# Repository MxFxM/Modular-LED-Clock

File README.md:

# Modular-LED-Clock
 Modular design for LED clocks.

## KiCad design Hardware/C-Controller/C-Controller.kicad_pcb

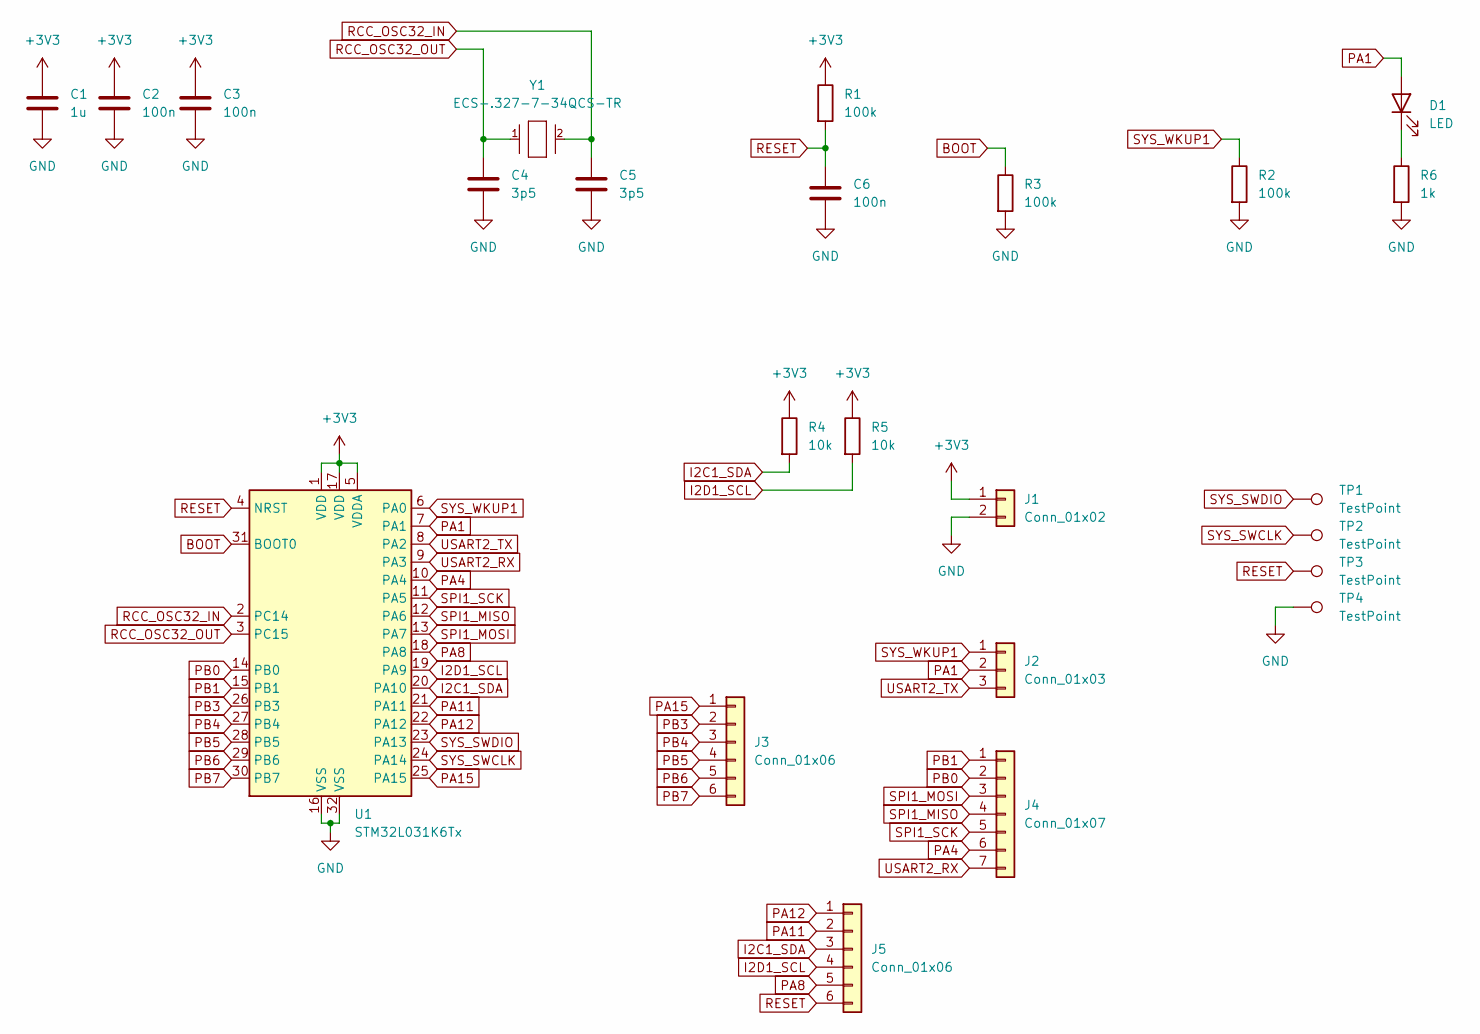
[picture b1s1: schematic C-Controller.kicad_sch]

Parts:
C1: 1u; C_0603_1608Metric
C2, C3, C6: 100n; C_0402_1005Metric
C4, C5: 3p5; C_0402_1005Metric
D1: LED; LED_0402_1005Metric
J1: Conn_01x02; PinSocket_1x02_P2.00mm_Vertical
J2: Conn_01x03; PinSocket_1x03_P1.00mm_Vertical
J3, J5: Conn_01x06; PinSocket_1x06_P1.00mm_Vertical
J4: Conn_01x07; PinSocket_1x07_P1.00mm_Vertical
R1, R2, R3: 100k; R_0402_1005Metric
R4, R5: 10k; R_0402_1005Metric
R6: 1k; R_0402_1005Metric
TP1, TP2, TP3, TP4: TestPoint; TestPoint_Pad_D1.0mm
U1: STM32L031K6Tx; LQFP-32_7x7mm_P0.8mm
Y1: ECS-.327-7-34QCS-TR; ECS_Inc.-ECX-34Q-0-0-0; tolerance 10ppm; mouser part number 520-.327-7-34QCST; digikey description CRYSTAL 32.768KHZ 7PF SMD

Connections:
+3V3: C1.1, C2.1, C3.1, J1.1, R1.1, R4.1, R5.1, U1.1 (VDD), U1.5 (VDDA), U1.17 (VDD)
BOOT: R3.1, U1.31 (BOOT0)
GND: C1.2, C2.2, C3.2, C4.2, C5.2, C6.2, J1.2, R2.2, R3.2, R6.2, TP4.1, U1.16 (VSS), U1.32 (VSS)
I2C1_SDA: J5.3, R4.2, U1.20 (PA10)
I2D1_SCL: J5.4, R5.2, U1.19 (PA9)
unnamed: D1.1 (K), R6.1
PA1: D1.2 (A), J2.2, U1.7 (PA1)
PA4: J4.6, U1.10 (PA4)
PA8: J5.5, U1.18 (PA8)
PA11: J5.2, U1.21 (PA11)
PA12: J5.1, U1.22 (PA12)
PA15: J3.1, U1.25 (PA15)
PB0: J4.2, U1.14 (PB0)
PB1: J4.1, U1.15 (PB1)
PB3: J3.2, U1.26 (PB3)
PB4: J3.3, U1.27 (PB4)
PB5: J3.4, U1.28 (PB5)
PB6: J3.5, U1.29 (PB6)
PB7: J3.6, U1.30 (PB7)
RCC_OSC32_IN: C5.1, U1.2 (PC14), Y1.2 (Out/In)
RCC_OSC32_OUT: C4.1, U1.3 (PC15), Y1.1 (In/Out)
RESET: C6.1, J5.6, R1.2, TP3.1, U1.4 (NRST)
SPI1_MISO: J4.4, U1.12 (PA6)
SPI1_MOSI: J4.3, U1.13 (PA7)
SPI1_SCK: J4.5, U1.11 (PA5)
SYS_SWCLK: TP2.1, U1.24 (PA14)
SYS_SWDIO: TP1.1, U1.23 (PA13)
SYS_WKUP1: J2.1, R2.1, U1.6 (PA0)
USART2_RX: J4.7, U1.9 (PA3)
USART2_TX: J2.3, U1.8 (PA2)

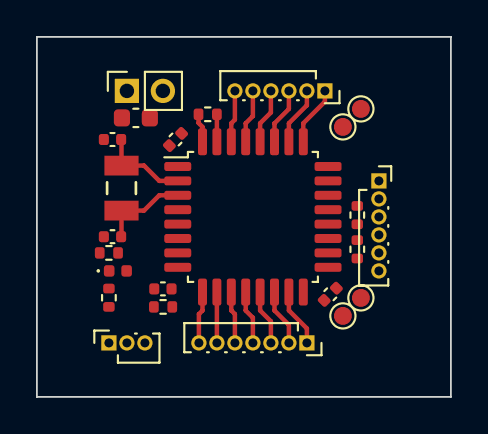
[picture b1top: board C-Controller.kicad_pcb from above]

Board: 2 copper layers, 23.0 x 20.0 mm, 24 parts (0 on the bottom side), 30 nets.

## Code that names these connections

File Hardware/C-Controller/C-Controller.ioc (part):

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Mcu.Name=STM32L031K(4-6)Tx
Mcu.Package=LQFP32
Mcu.UserName=STM32L031K6Tx
PA0-CK_IN.Mode=SYS_WakeUp0
PA0-CK_IN.Signal=SYS_WKUP1
PA10.Mode=I2C
PA10.Signal=I2C1_SDA
PA13.Mode=Serial_Wire
PA13.Signal=SYS_SWDIO
PA14.Mode=Serial_Wire
PA14.Signal=SYS_SWCLK
PA2.Mode=Asynchronous
PA2.Signal=USART2_TX
PA3.Mode=Asynchronous
PA3.Signal=USART2_RX
PA5.Mode=Full_Duplex_Master
PA5.Signal=SPI1_SCK
PA6.Mode=Full_Duplex_Master
PA6.Signal=SPI1_MISO
PA7.Mode=Full_Duplex_Master
PA7.Signal=SPI1_MOSI
PA9.Mode=I2C
PA9.Signal=I2C1_SCL
PC14-OSC32_IN.Mode=LSE-External-Oscillator
PC14-OSC32_IN.Signal=RCC_OSC32_IN
PC15-OSC32_OUT.Mode=LSE-External-Oscillator
PC15-OSC32_OUT.Signal=RCC_OSC32_OUT
RCC.HSE_VALUE=8000000
RCC.SYSCLKFreq_VALUE=2097000
board=custom

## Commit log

2022-01-22 created empty projects to implement a folder structure
2022-01-22 gitignore for all kicad backups in the hardware folder
2022-01-22 crystal missing
2022-01-22 1mm pitch headers
2022-01-29 smaller components, crystal lib, status led, smaller board
